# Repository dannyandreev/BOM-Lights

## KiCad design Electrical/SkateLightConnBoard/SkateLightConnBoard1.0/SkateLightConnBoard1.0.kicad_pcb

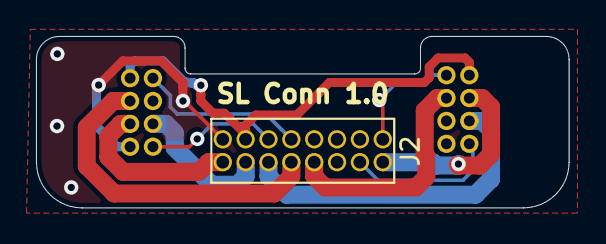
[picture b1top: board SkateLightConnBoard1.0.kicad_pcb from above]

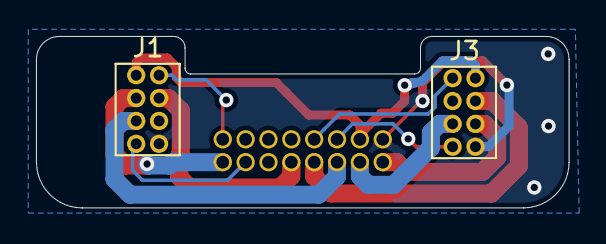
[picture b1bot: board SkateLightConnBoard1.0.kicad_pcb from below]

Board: 2 copper layers, 29.6 x 9.5 mm, 3 parts (2 on the bottom side), 12 nets.

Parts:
J1, J3: Conn_02x04_Odd_Even; Conn_2x4_0.05in
J2: Conn_02x08_Odd_Even; Conn_2x8_0.05in

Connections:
+3V3: J1.1, J2.13, J3.2
GND: J1.8, J2.15, J3.8
LED1A: J1.3, J2.2
LED1C: J1.5, J2.12
LED2A: J1.4, J2.8
LED2C: J2.14, J3.5
LED3A: J2.10, J3.4
LED3C: J2.16, J3.6
LightSense1: J1.2, J2.1
LightSense2: J2.9, J3.1
temp1: J1.7, J2.4
temp2: J2.11, J3.7

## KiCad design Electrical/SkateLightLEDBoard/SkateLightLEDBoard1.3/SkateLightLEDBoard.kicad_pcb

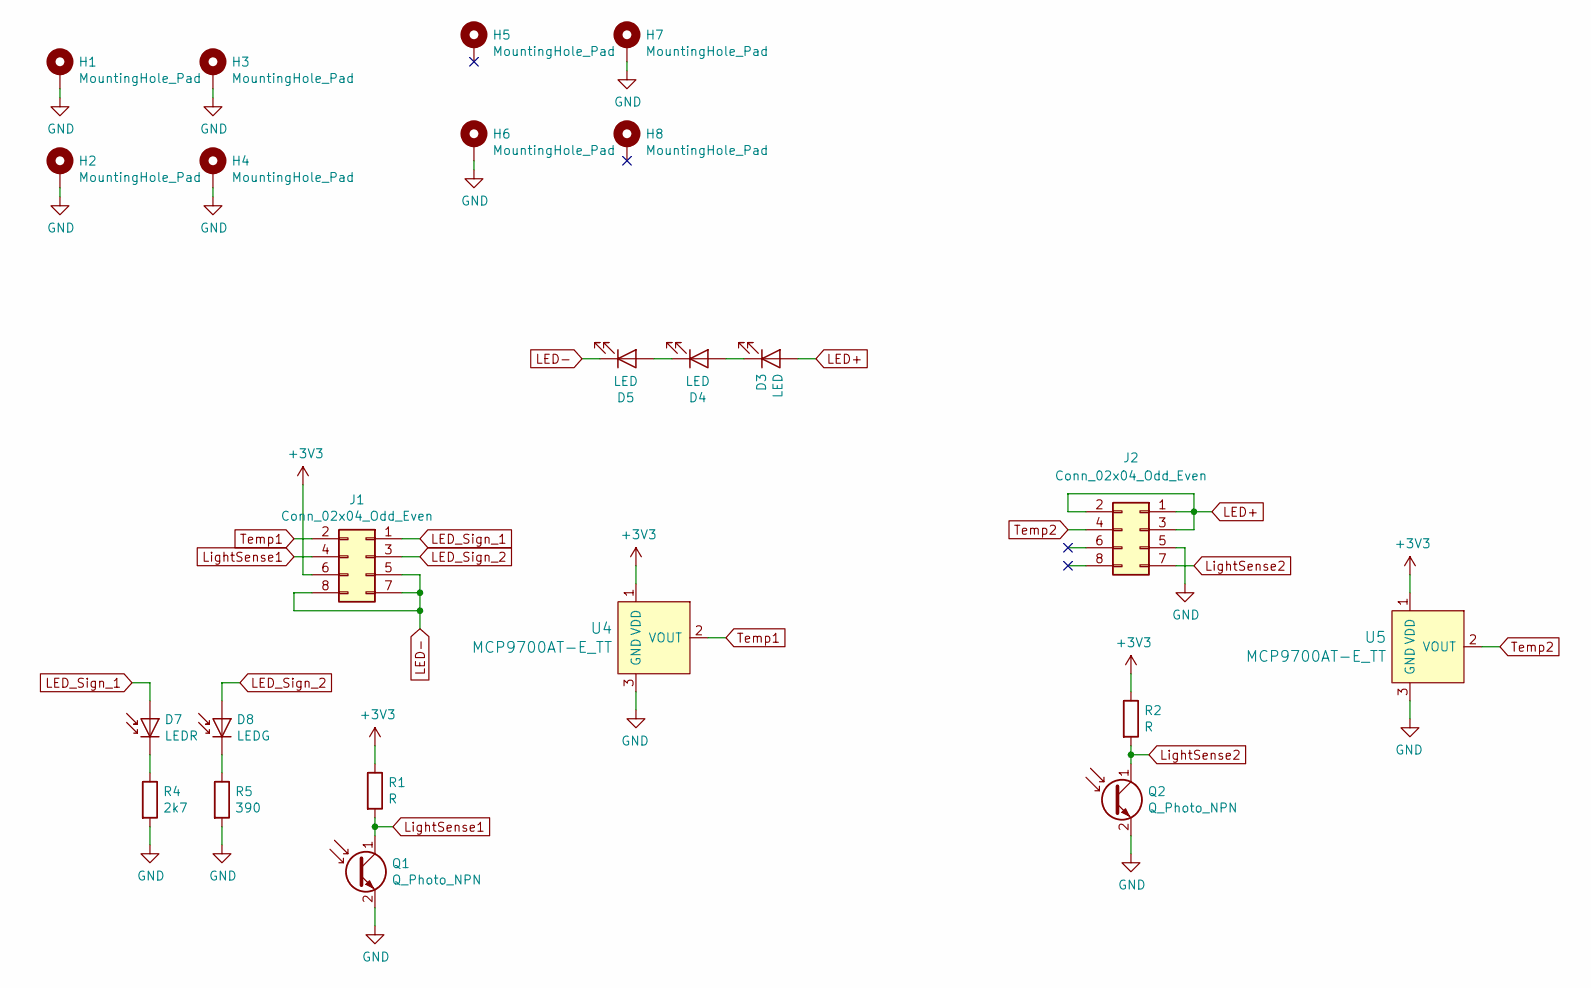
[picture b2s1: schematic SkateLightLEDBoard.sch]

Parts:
D3, D4, D5: LED; BXRE-40E0800-D-73
D7: LEDR; D_0402_1005Metric
D8: LEDG; D_0402_1005Metric
H1, H2, H3, H4, H5, H6, H7, H8: MountingHole_Pad; MH_0-80_Screw_Grounded
J1, J2: Conn_02x04_Odd_Even; Conn_2x4_0.05in
Q1, Q2: Q_Photo_NPN; D_0603_1608Metric
R1, R2: R; R_0402_1005Metric
R4: 2k7; R_0402_1005Metric
R5: 390; R_0402_1005Metric
U4, U5: MCP9700AT-E_TT; SOT-23; MPN MCP9700AT-E/TT; Digi-Key_PN MCP9700AT-E/TTCT-ND

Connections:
+3V3: J1.6, R1.1, R2.1, U4.1 (VDD), U5.1 (VDD)
GND: H1.1, H2.1, H3.1, H4.1, H6.1, H7.1, J2.5, Q1.2 (E), Q2.2 (E), R4.2, R5.2, U4.3 (GND), U5.3 (GND)
LED+: D3.2 (A), J2.1, J2.2, J2.3
LED-: D5.1 (K), J1.5, J1.7, J1.8
LED_Sign_1: D7.2 (A), J1.1
LED_Sign_2: D8.2 (A), J1.3
LightSense1: J1.4, Q1.1 (C), R1.2
LightSense2: J2.7, Q2.1 (C), R2.2
unnamed: D3.1 (K), D4.2 (A)
unnamed: D4.1 (K), D5.2 (A)
unnamed: D7.1 (K), R4.1
unnamed: D8.1 (K), R5.1
Temp1: J1.2, U4.2 (VOUT)
Temp2: J2.4, U5.2 (VOUT)

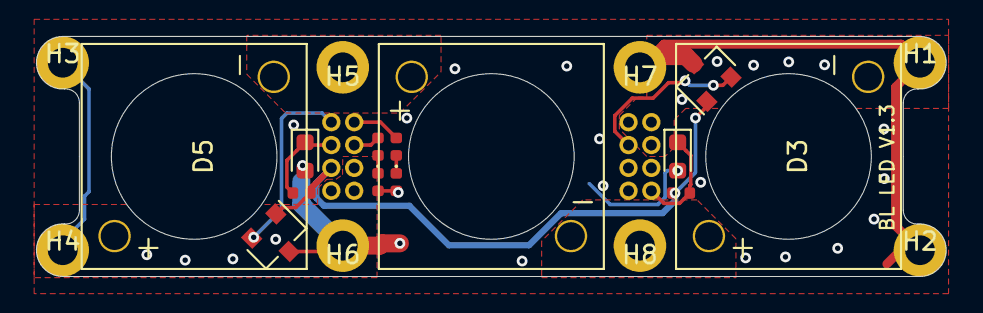
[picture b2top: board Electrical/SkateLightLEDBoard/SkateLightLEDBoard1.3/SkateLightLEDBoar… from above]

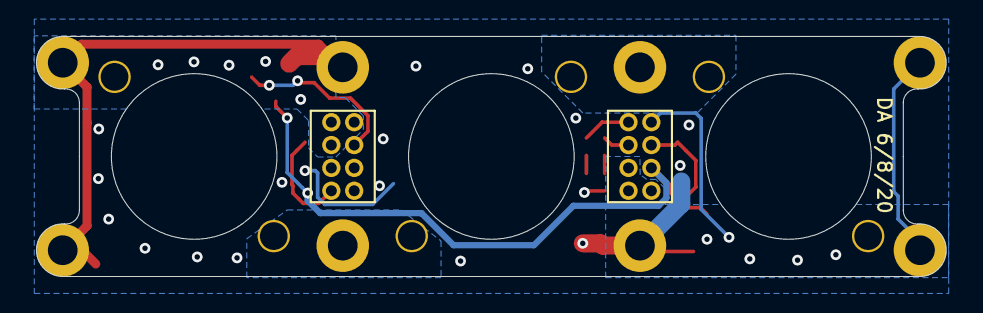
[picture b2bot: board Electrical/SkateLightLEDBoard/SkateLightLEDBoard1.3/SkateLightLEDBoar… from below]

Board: 2 copper layers, 50.5 x 13.3 mm, 23 parts (2 on the bottom side), 14 nets.

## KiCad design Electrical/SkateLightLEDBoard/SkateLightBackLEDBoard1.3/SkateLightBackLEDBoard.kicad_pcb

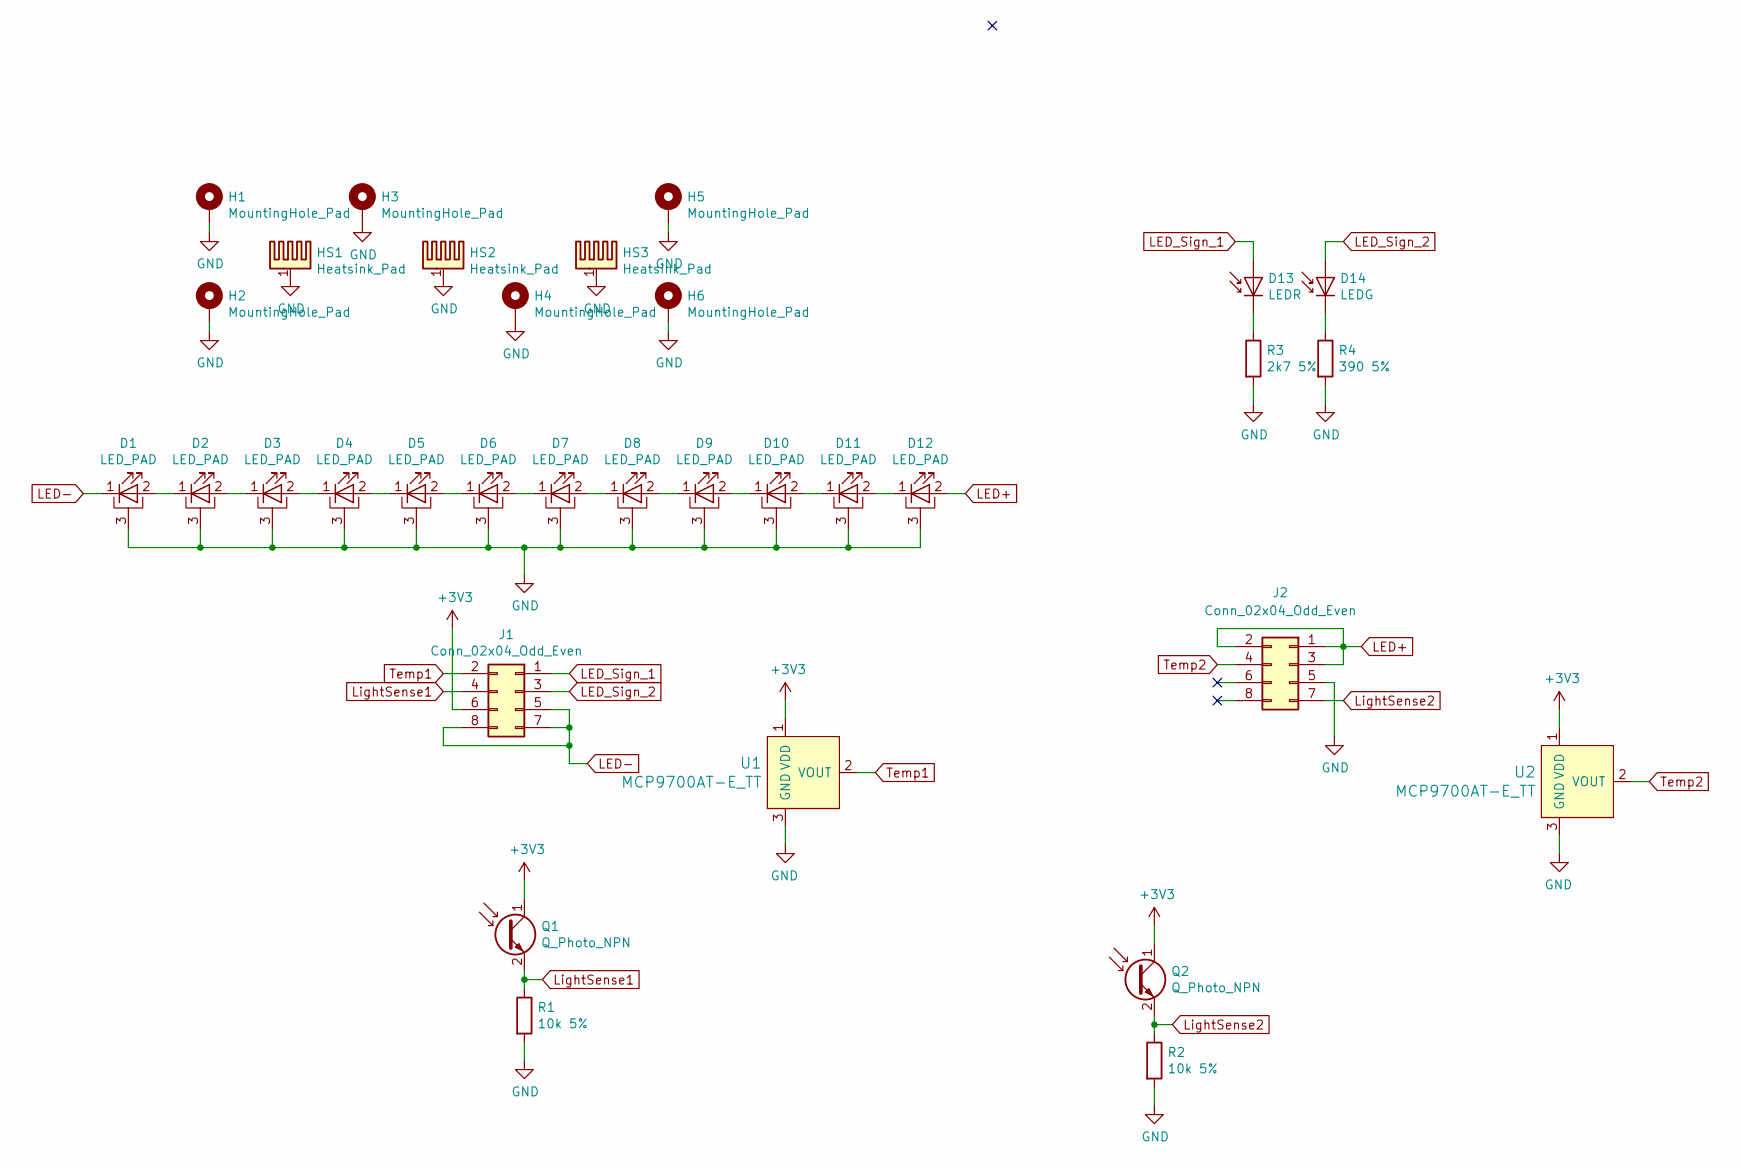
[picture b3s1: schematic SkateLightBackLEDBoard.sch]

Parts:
D1, D2, D3, D4, D5, D6, D7, D8, D9, D10, D11, D12: LED_PAD; SST-10-DR-B90-G660
D13: LEDR; D_0402_1005Metric
D14: LEDG; D_0402_1005Metric
H1, H2, H3, H4, H5, H6: MountingHole_Pad; MH_0-80_Screw_Grounded
HS1, HS2, HS3: Heatsink_Pad; BomLightBackLEDHeatsink
J1, J2: Conn_02x04_Odd_Even; Conn_2x4_0.05in
Q1, Q2: Q_Photo_NPN; D_0603_1608Metric
R1, R2: 10k 5%; R_0402_1005Metric
R3: 2k7 5%; R_0402_1005Metric
R4: 390 5%; R_0402_1005Metric
U1, U2: MCP9700AT-E_TT; SOT-23; MPN MCP9700AT-E/TT; Digi-Key_PN MCP9700AT-E/TTCT-ND

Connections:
+3V3: J1.6, Q1.1 (C), Q2.1 (C), U1.1 (VDD), U2.1 (VDD)
GND: D1.3 (PAD), D2.3 (PAD), D3.3 (PAD), D4.3 (PAD), D5.3 (PAD), D6.3 (PAD), D7.3 (PAD), D8.3 (PAD), D9.3 (PAD), D10.3 (PAD), D11.3 (PAD), D12.3 (PAD), H1.1, H2.1, H3.1, H4.1, H5.1, H6.1, HS1.1, HS2.1, HS3.1, J2.5, R1.2, R2.2, R3.2, R4.2, U1.3 (GND), U2.3 (GND)
LED+: D12.2 (A), J2.1, J2.2, J2.3
LED-: D1.1 (K), J1.5, J1.7, J1.8
LED_Sign_1: D13.2 (A), J1.1
LED_Sign_2: D14.2 (A), J1.3
LightSense1: J1.4, Q1.2 (E), R1.1
LightSense2: J2.7, Q2.2 (E), R2.1
unnamed: D1.2 (A), D2.1 (K)
unnamed: D2.2 (A), D3.1 (K)
unnamed: D3.2 (A), D4.1 (K)
unnamed: D4.2 (A), D5.1 (K)
unnamed: D5.2 (A), D6.1 (K)
unnamed: D6.2 (A), D7.1 (K)
unnamed: D7.2 (A), D8.1 (K)
unnamed: D8.2 (A), D9.1 (K)
unnamed: D9.2 (A), D10.1 (K)
unnamed: D10.2 (A), D11.1 (K)
unnamed: D11.2 (A), D12.1 (K)
unnamed: D13.1 (K), R3.1
unnamed: D14.1 (K), R4.1
Temp1: J1.2, U1.2 (VOUT)
Temp2: J2.4, U2.2 (VOUT)

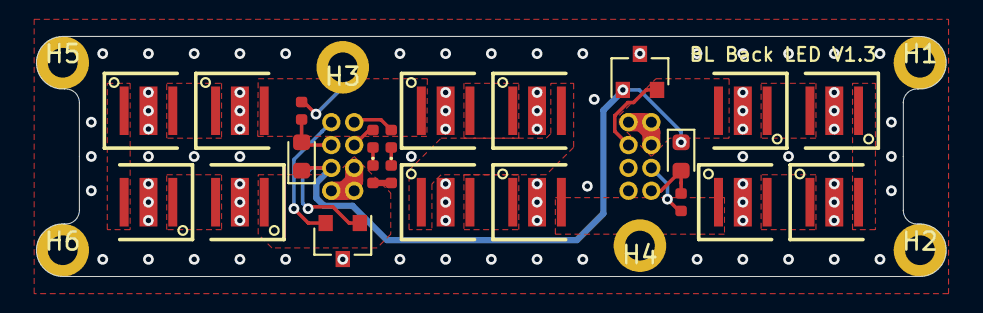
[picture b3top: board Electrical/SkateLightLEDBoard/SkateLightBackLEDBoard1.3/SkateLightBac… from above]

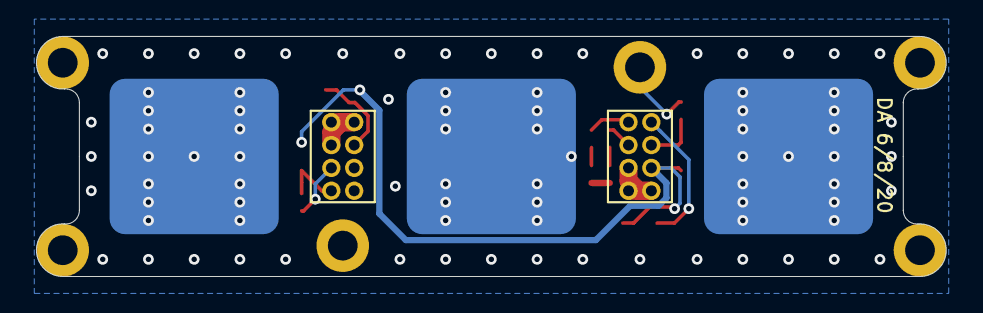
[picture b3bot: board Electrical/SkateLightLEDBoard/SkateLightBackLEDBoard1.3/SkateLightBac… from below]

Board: 2 copper layers, 50.5 x 13.3 mm, 33 parts (5 on the bottom side), 23 nets.

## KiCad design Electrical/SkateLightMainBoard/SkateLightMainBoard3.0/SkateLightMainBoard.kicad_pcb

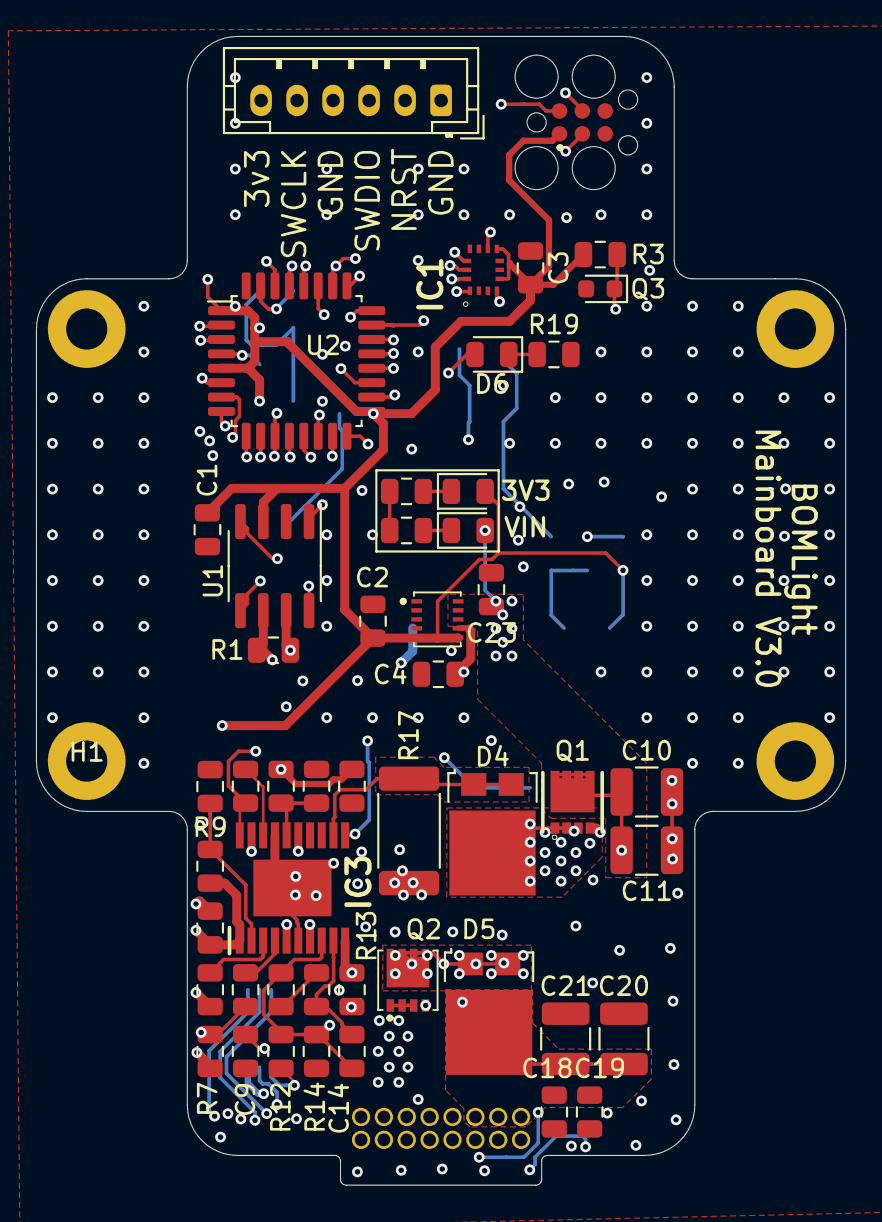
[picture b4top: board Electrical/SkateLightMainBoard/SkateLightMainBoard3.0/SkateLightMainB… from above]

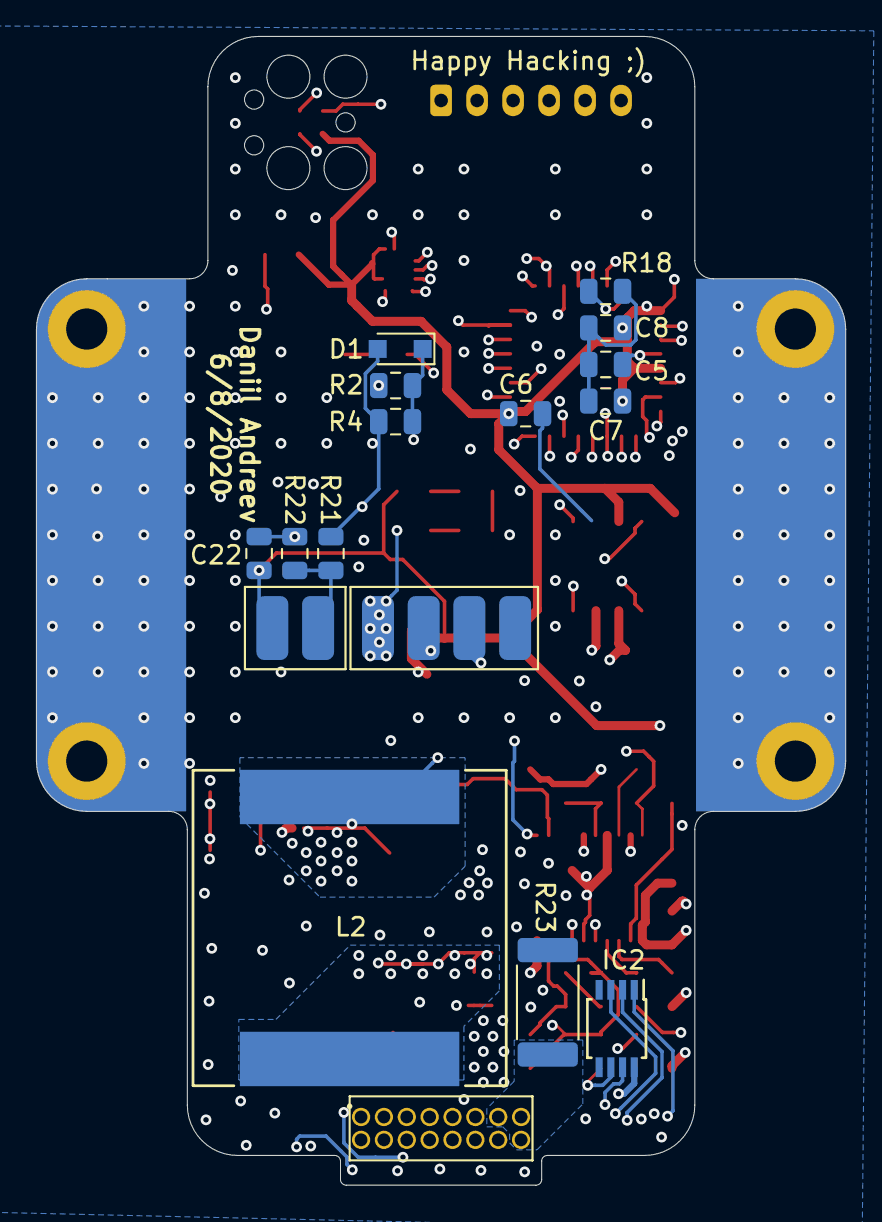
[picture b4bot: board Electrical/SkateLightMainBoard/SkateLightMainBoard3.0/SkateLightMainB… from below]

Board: 4 copper layers, 45.0 x 63.8 mm, 68 parts (17 on the bottom side), 55 nets.

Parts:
C1, C3, C5, C6, C7, C8, C15, C22: 100nF; C_0805_2012Metric
C2: 10uF; C_0805_2012Metric
C4, C17, C23: 1uF; C_0805_2012Metric
C9: 22nF; C_0805_2012Metric
C10, C11, C20, C21: 10uF; C_1210_3225Metric
C12: 0.1uF; C_0805_2012Metric
C13: 220nF; C_0805_2012Metric
C14: 6.8nF; C_0805_2012Metric
C16: 2.2nF; C_0805_2012Metric
C18, C19: 0.47uF; C_0805_2012Metric
D1: D_Zener; D_SOD-323_HandSoldering
D2, D3: LEDO; LED_0805_2012Metric
D4, D5: D_Schottky_AAK; TO-277A
D6: LEDR; LED_0805_2012Metric
H1, H2: MountingHole_Pad; ThermalPadV2_SkateLight
IC1: LSM6DS3USTR; LGA-14(2.5X3X0.86)
IC2: MCP4132-502E_SN; TSSOP-8_3x3mm_P0.65mm
IC3: LM5118MH_NOPB; SOP65P640X110-21N
IC4: MAXM15062AMB+; MAXM15462AMB
J1: Conn_01x04_Male; 4 Wire Pad
J2: TC2030-MCP; TC2030MCP
J3: Conn_01x02_Male; 2WirePad
J4: Conn_02x08_Odd_Even; Conn_2x8_0.05in
J5: Conn_01x06_Male; JST_PH_B6B-PH-K_1x06_P2.00mm_Vertical
L2: IHLP6767GZER470M11
Q1: CSD19537Q3; DQG_VSON-CLIP
Q2: FDMC86240; FDMC86139P
Q3: Q_Photo_NPN; D_0603_1608Metric
R1: 120; R_0805_2012Metric
R2, R14, R21: 100k; R_0805_2012Metric
R3: R; R_0805_2012Metric
R4: 180k; R_0805_2012Metric
R5: 33k; R_0805_2012Metric
R6: 1k2; R_0805_2012Metric
R7: 47k; R_0805_2012Metric
R8: 1k; R_0805_2012Metric
R9: 68k; R_0805_2012Metric
R10, R18, R22: 10k; R_0805_2012Metric
R11: 20k5; R_0805_2012Metric
R12: 4k7; R_0805_2012Metric
R13: 220k; R_0805_2012Metric
R15: 5k62; R_0805_2012Metric
R16: 36k5; R_0805_2012Metric
R17: 0.05; R_2512_6332Metric
R19: 1k5; R_0805_2012Metric
R23: .5; R_2512_6332Metric
U1: SN65HVD233; SOIC-8_3.9x4.9mm_P1.27mm
U2: STM32F042K6Tx; LQFP-32_7x7mm_P0.8mm

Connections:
+3V3: C1.1, C2.1, C3.1, C6.1, C7.1, C8.1, C22.1, D3.2, IC1.5, IC1.8, IC2.8, IC4.5, IC4.6, J2.1, J3.2, J4.13, J5.6, R3.1, U1.3, U2.1, U2.5, U2.17
Button: C22.2, R22.1, U2.8
CAN_LBK: U1.5, U2.19
CAN_RX: U1.4, U2.22
CAN_Rs: U1.8, U2.20
CAN_TX: U1.1, U2.21
GND: C1.2, C2.2, C3.2, C4.2, C5.2, C6.2, C7.2, C8.2, C9.2, C10.2, C11.2, C12.2, C16.2, C17.2, C18.2, C19.2, C20.2, C21.2, C23.2, D1.2, H1.1, H2.1, IC1.2, IC1.3, IC1.6, IC1.7, IC2.4, IC2.5, IC3.6, IC3.13, IC3.14, IC3.17, IC3.21, IC4.2, J1.1, J2.5, J4.7, J5.1, J5.4, Q2.1, Q2.2, Q2.3, Q3.2, R4.2, R5.2, R6.2, R7.2, R10.2, R11.2, R14.2, R17.2, R18.2, R19.2, R21.1, R23.2, U1.2, U2.16, U2.32
IMU_INT1: IC1.4, U2.14
IMU_INT2: IC1.9, U2.18
LED+: C18.1, C19.1, C20.1, C21.1, D5.3, IC3.10, J4.2, J4.4, J4.6, R13.1
LED-: J4.14, J4.15, J4.16, R23.1, U2.12
LEDCTRL: R7.1, R8.2, U2.13
LEDR: D6.2, U2.25
LEDSign1: J4.11, U2.2
LEDSign2: J4.12, U2.3
LightSense1: J4.8, U2.7
LightSense2: J4.9, U2.9
LightSense3: J4.5, Q3.1, R3.2, U2.11
NRST: C5.1, J2.3, J5.2, U2.4
unnamed: C4.1, IC4.7
unnamed: C9.1, IC3.7
unnamed: C13.1, R15.2
unnamed: C13.2, C14.2, IC3.8, R12.1, R13.2, R14.1
unnamed: C14.1, IC3.9, R15.1
unnamed: C15.1, D4.3, IC3.20, L2.2, Q1.1, Q1.2, Q1.3
unnamed: C15.2, IC3.18
unnamed: C16.1, IC3.5, R16.2
unnamed: C17.1, IC3.16, R16.1
unnamed: D1.1, R2.1, R4.1, U2.15
unnamed: D2.1, R5.1
unnamed: D3.1, R6.1
unnamed: D4.1, D4.2, IC3.12, R17.1
unnamed: D5.1, D5.2, L2.1, Q2.5, Q2.6, Q2.7, Q2.8
unnamed: D6.1, R19.1
unnamed: IC2.6, R12.2
unnamed: IC3.2, R9.2, R10.1
unnamed: IC3.3, R11.1
unnamed: IC3.4, R8.1
unnamed: IC3.15, Q2.4
unnamed: IC3.19, Q1.4
unnamed: J1.2, R1.1, U1.6
unnamed: J1.3, R1.2, U1.7
unnamed: J3.1, R21.2, R22.2
unnamed: R18.1, U2.31
SPI1_DPOT_CS: IC2.1, U2.30
SPI1_IMU_CS: IC1.12, U2.29
SPI1_MISO: IC1.1, IC2.7, U2.27
SPI1_MOSI: IC1.14, IC2.3, U2.28
SPI1_SCK: IC1.13, IC2.2, U2.26
SWCLK: J2.4, J5.5, U2.24
SWDIO: J2.2, J5.3, U2.23
SYNC: IC3.11, R2.2
Temp1: J4.10, U2.6
Temp2: J4.1, U2.10
VCC: C10.1, C11.1, C12.1, C23.1, D2.2, IC3.1, IC4.8, IC4.9, IC4.10, J1.4, Q1.5, Q1.6, Q1.7, Q1.8, R9.1

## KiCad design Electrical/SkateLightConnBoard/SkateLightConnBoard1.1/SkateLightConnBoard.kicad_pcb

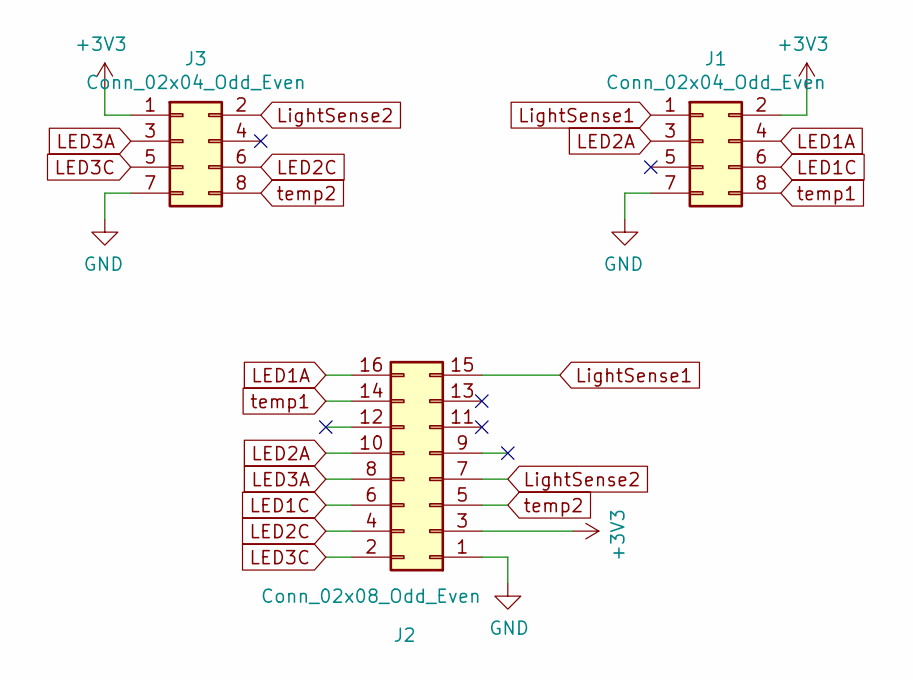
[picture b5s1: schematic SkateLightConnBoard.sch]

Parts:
J1, J3: Conn_02x04_Odd_Even; Conn_2x4_0.05in
J2: Conn_02x08_Odd_Even; Conn_2x8_0.05in

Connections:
+3V3: J1.2, J2.3, J3.1
GND: J1.7, J2.1, J3.7
LED1A: J1.4, J2.16
LED1C: J1.6, J2.6
LED2A: J1.3, J2.10
LED2C: J2.4, J3.6
LED3A: J2.8, J3.3
LED3C: J2.2, J3.5
LightSense1: J1.1, J2.15
LightSense2: J2.7, J3.2
temp1: J1.8, J2.14
temp2: J2.5, J3.8

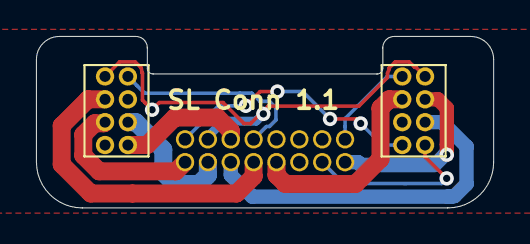
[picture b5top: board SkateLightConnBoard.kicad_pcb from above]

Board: 2 copper layers, 25.4 x 9.5 mm, 3 parts (1 on the bottom side), 12 nets.

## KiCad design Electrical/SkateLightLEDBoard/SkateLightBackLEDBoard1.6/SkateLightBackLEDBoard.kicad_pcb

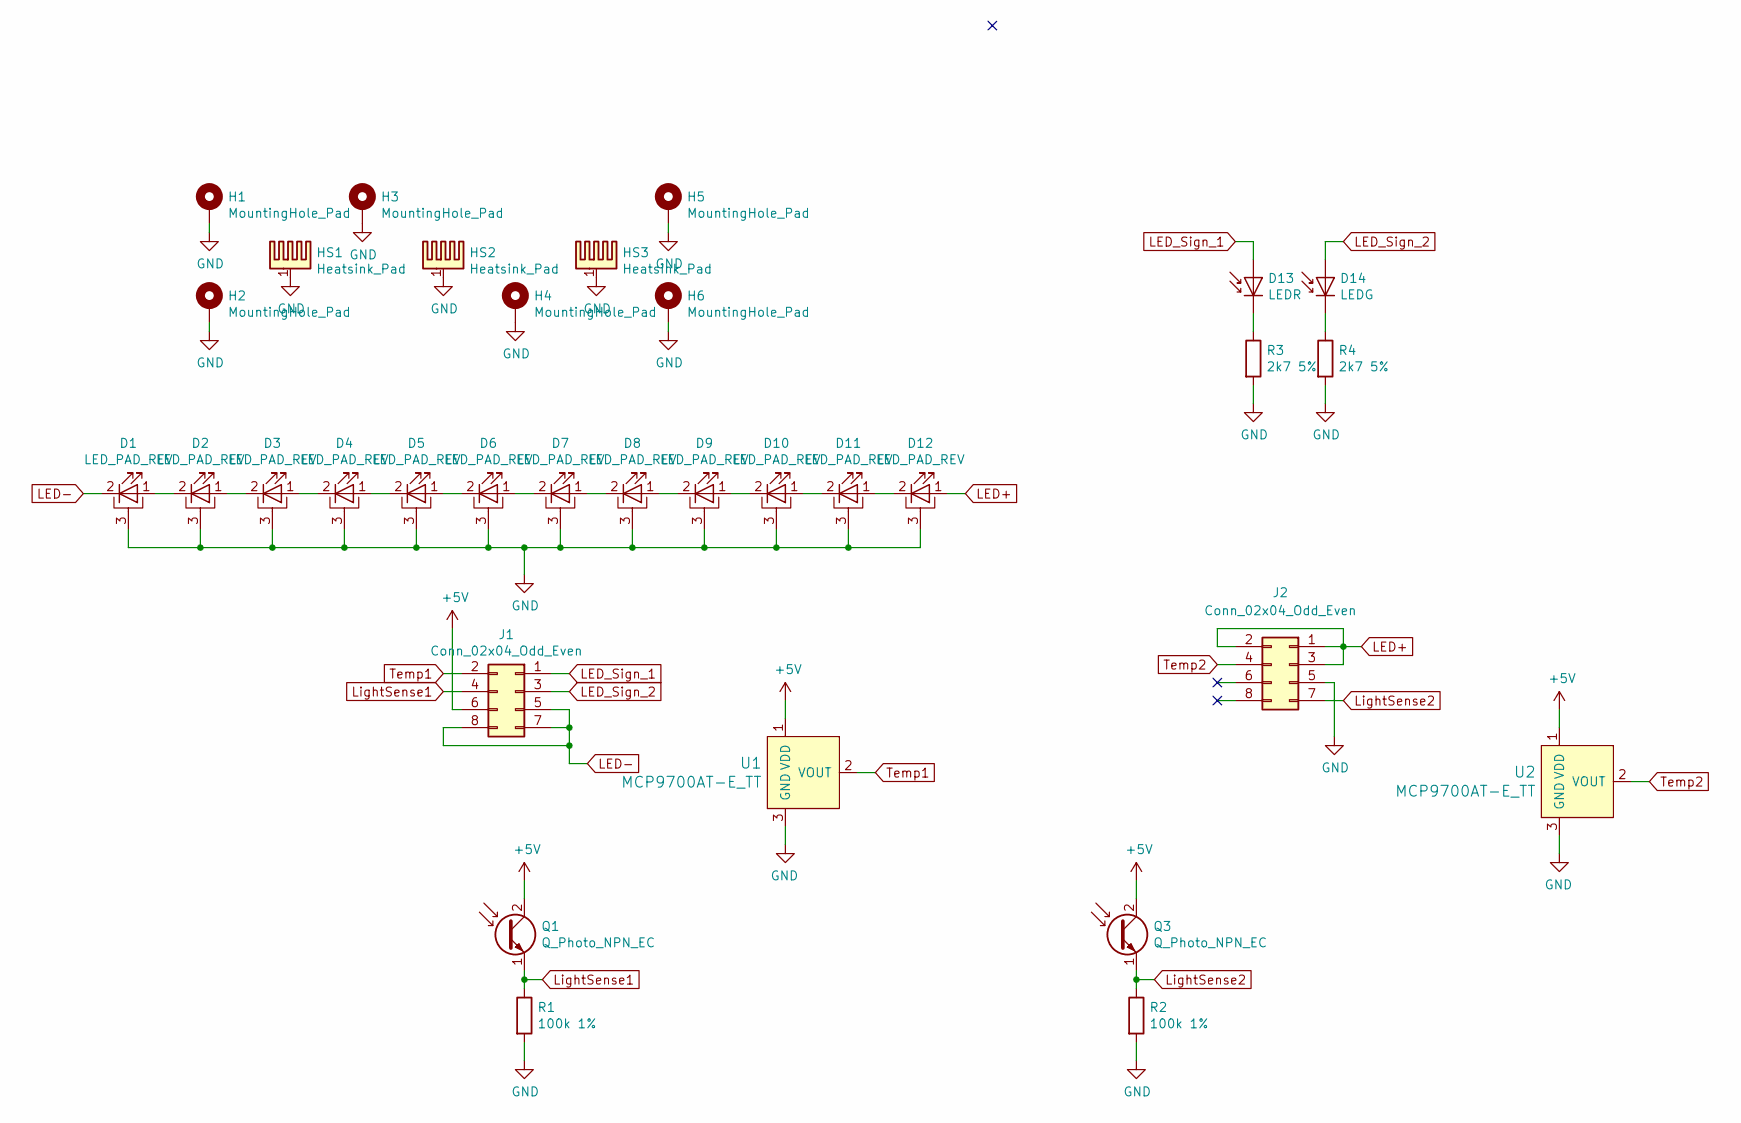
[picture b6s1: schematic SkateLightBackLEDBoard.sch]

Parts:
D1, D2, D3, D4, D5, D6, D7, D8, D9, D10, D11, D12: LED_PAD_REV; SST-10-DR-B90-G660
D13: LEDR; D_0402_1005Metric
D14: LEDG; D_0402_1005Metric
H1, H2, H3, H4, H5, H6: MountingHole_Pad; MH_0-80_Screw_Grounded
HS1, HS2, HS3: Heatsink_Pad; BomLightBackLEDHeatsink
J1, J2: Conn_02x04_Odd_Even; Conn_2x4_0.05in
Q1, Q3: Q_Photo_NPN_EC; D_0603_1608Metric
R1, R2: 100k 1%; R_0402_1005Metric
R3, R4: 2k7 5%; R_0402_1005Metric
U1, U2: MCP9700AT-E_TT; SOT-23; MPN MCP9700AT-E/TT; Digi-Key_PN MCP9700AT-E/TTCT-ND

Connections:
+5V: J1.6, Q1.2 (C), Q3.2 (C), U1.1 (VDD), U2.1 (VDD)
GND: D1.3 (PAD), D2.3 (PAD), D3.3 (PAD), D4.3 (PAD), D5.3 (PAD), D6.3 (PAD), D7.3 (PAD), D8.3 (PAD), D9.3 (PAD), D10.3 (PAD), D11.3 (PAD), D12.3 (PAD), H1.1, H2.1, H3.1, H4.1, H5.1, H6.1, HS1.1, HS2.1, HS3.1, J2.5, R1.2, R2.2, R3.2, R4.2, U1.3 (GND), U2.3 (GND)
LED+: D12.1 (K), J2.1, J2.2, J2.3
LED-: D1.2 (A), J1.5, J1.7, J1.8
LED_Sign_1: D13.2 (A), J1.1
LED_Sign_2: D14.2 (A), J1.3
LightSense1: J1.4, Q1.1 (E), R1.1
LightSense2: J2.7, Q3.1 (E), R2.1
unnamed: D1.1 (K), D2.2 (A)
unnamed: D2.1 (K), D3.2 (A)
unnamed: D3.1 (K), D4.2 (A)
unnamed: D4.1 (K), D5.2 (A)
unnamed: D5.1 (K), D6.2 (A)
unnamed: D6.1 (K), D7.2 (A)
unnamed: D7.1 (K), D8.2 (A)
unnamed: D8.1 (K), D9.2 (A)
unnamed: D10.1 (K), D11.2 (A)
unnamed: D9.1 (K), D10.2 (A)
unnamed: D11.1 (K), D12.2 (A)
unnamed: D13.1 (K), R3.1
unnamed: D14.1 (K), R4.1
Temp1: J1.2, U1.2 (VOUT)
Temp2: J2.4, U2.2 (VOUT)

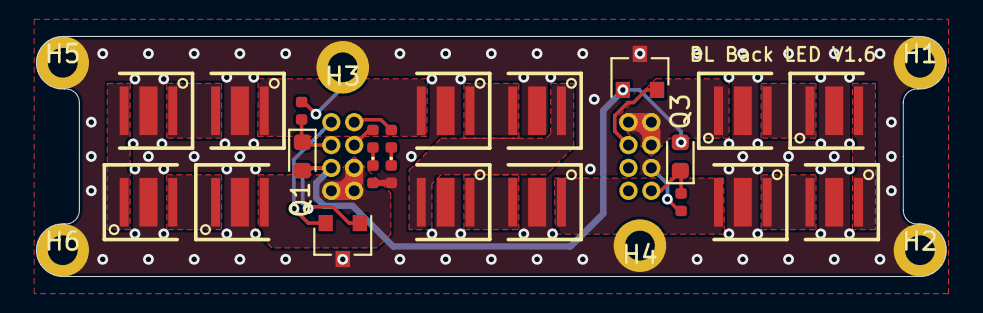
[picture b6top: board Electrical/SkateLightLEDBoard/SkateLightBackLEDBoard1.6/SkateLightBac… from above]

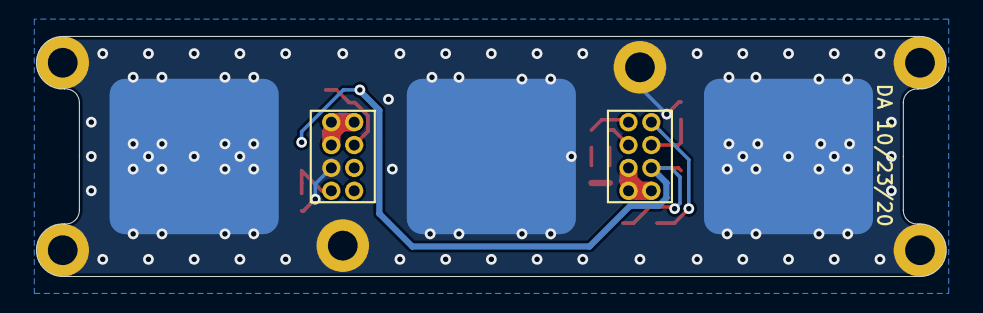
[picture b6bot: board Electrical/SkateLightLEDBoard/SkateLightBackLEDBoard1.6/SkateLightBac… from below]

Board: 2 copper layers, 50.5 x 13.3 mm, 33 parts (5 on the bottom side), 23 nets.

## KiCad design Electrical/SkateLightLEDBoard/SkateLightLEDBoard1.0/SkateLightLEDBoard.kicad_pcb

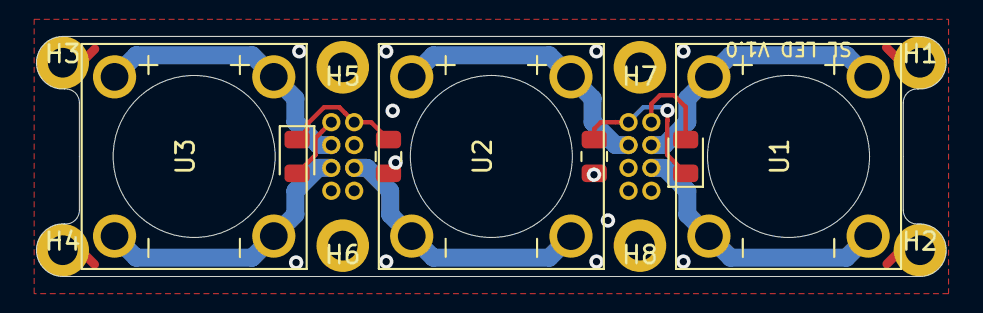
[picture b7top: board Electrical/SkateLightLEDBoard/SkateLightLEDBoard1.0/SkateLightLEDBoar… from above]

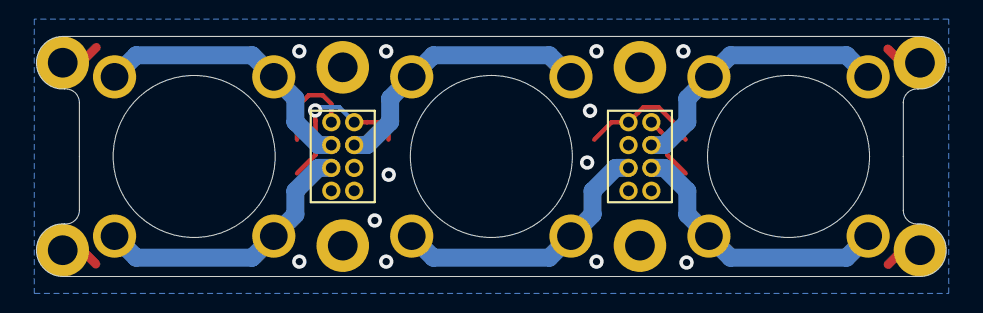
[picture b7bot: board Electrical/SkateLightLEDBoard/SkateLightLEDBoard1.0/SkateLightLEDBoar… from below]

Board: 2 copper layers, 50.5 x 13.3 mm, 17 parts (2 on the bottom side), 11 nets.

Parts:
D1, D2: D_Photo; D_0805_2012Metric
H1, H2, H3, H4, H5, H6, H7, H8: MountingHole_Pad; MH_0-80_Screw_Grounded
J1, J2: Conn_02x04_Odd_Even; Conn_2x4_0.05in
R1, R2: R; R_0805_2012Metric
U1, U2, U3: LED_4PinPackage; BXRE-40E0800-D-73

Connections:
3V3_1: D1.2, J1.1
3V3_2: D2.2, J2.2
GND: H1.1, H2.1, H3.1, H4.1, H5.1, H6.1, H7.1, H8.1, J1.8, J2.8, R1.2, R2.2
LED1A: J1.3, U1.1, U1.2
LED1C: J1.5, U1.3, U1.4
LED2A: J1.4, U2.1, U2.2
LED2C: J2.5, U2.3, U2.4
LED3A: J2.4, U3.1, U3.2
LED3C: J2.6, U3.3, U3.4
LightSense1: D1.1, J1.2, R1.1
LightSense2: D2.1, J2.1, R2.1

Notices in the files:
parts and their libraries:
Copyright 2016 Accelerated Designs. All rights reserved.
